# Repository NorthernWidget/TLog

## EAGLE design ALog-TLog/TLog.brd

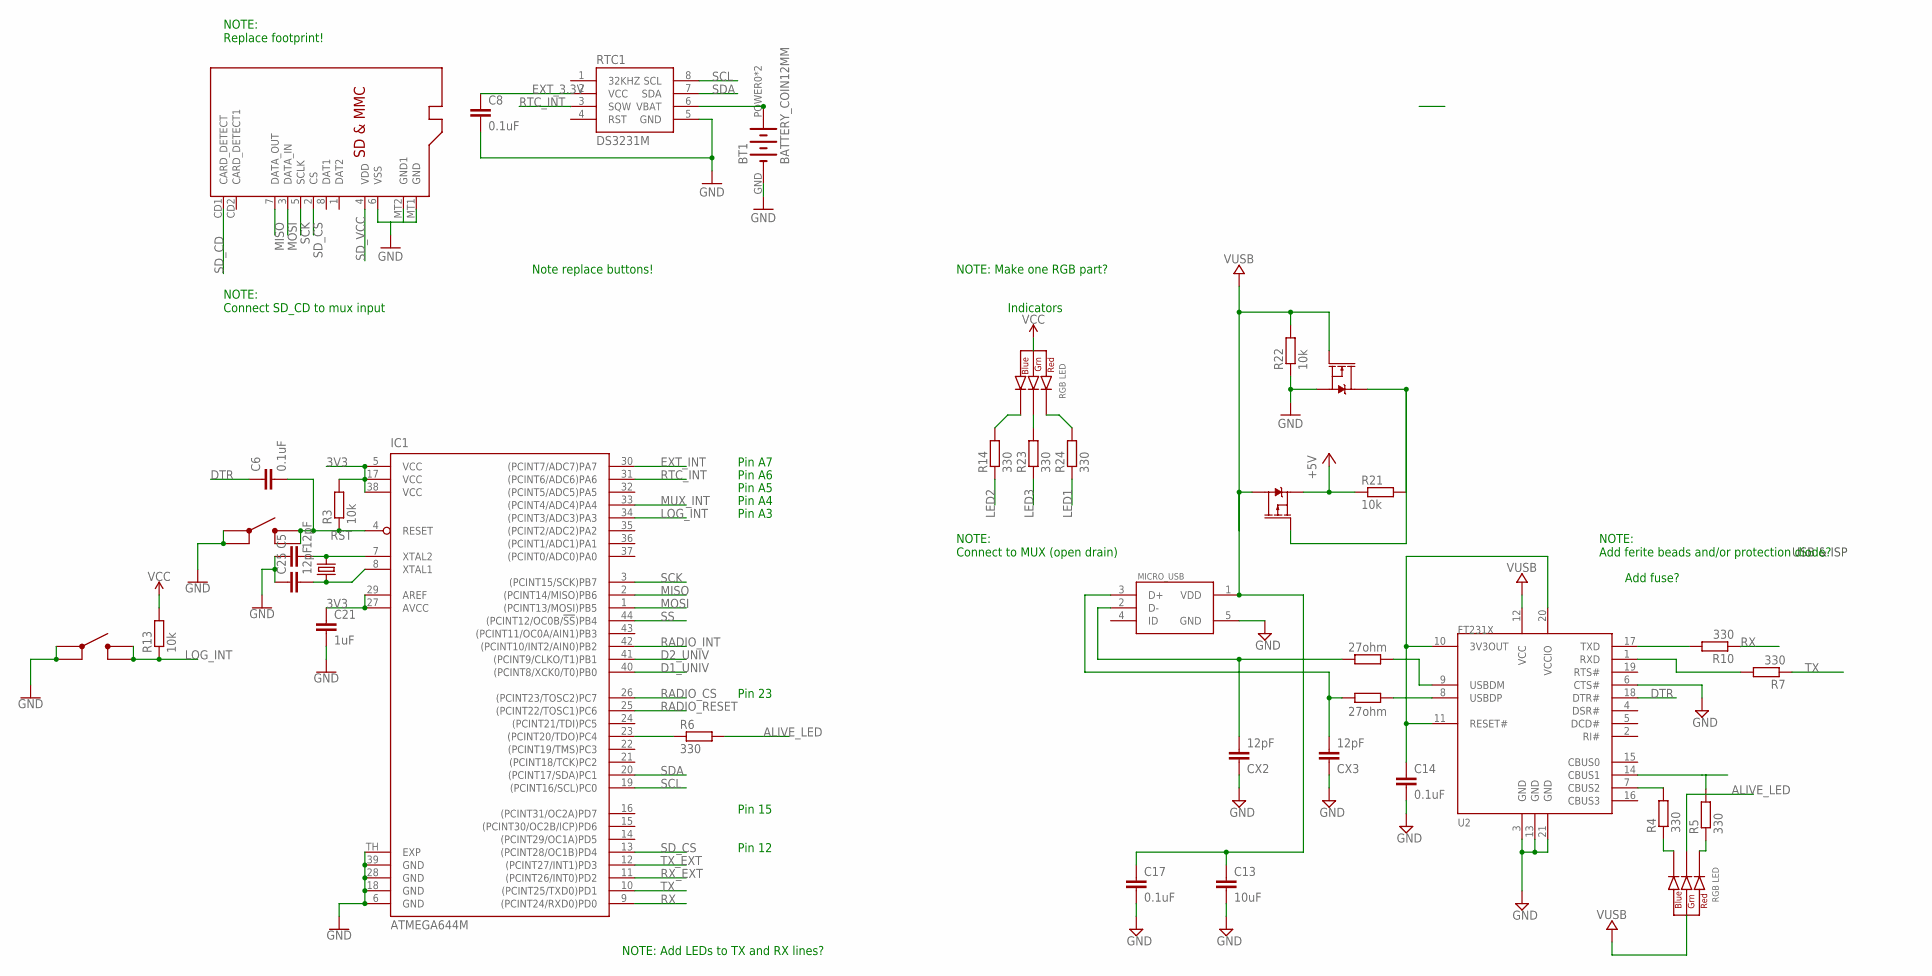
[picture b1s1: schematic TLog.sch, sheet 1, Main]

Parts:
BT1: BATTERY_COIN12MM; AWICKERT_LINX_BAT-HLD-012-SMT
C5, C25: 12pF; C0603; MPN CL10C120JB8NNNC; DIGIKEY 1276-1254-1-ND
C6, C8, C14, C17: 0.1uF; C0603
C13: 10uF; C0805
C21: 1uF; C0603; MPN CL10B105MO8NNWC; DIGIKEY 1276-6524-1-ND
CX2, CX3: 12pF; C0603
D+: 27ohm; R0603
D-: 27ohm; R0603
IC1: ATMEGA644M; MLF44-TH
MICRO_USB: MICRO_USB_LONGPADS; 10118194-0001LF_10118194-0001LF_LONGER_PADS
Q11: MOSFET-NCH-BSS138; SOT23-3
Q12: MOSFET_PCH-IRLML2244; SOT23-3
R3, R13: 10k; R0603; DIGIKEY 311-10.0KHRCT-ND
R4, R7, R10, R14, R23, R24: 330; R0603; MPN RC0603FR-07330RL
R5: 330; R0603; MPN RC0603FR-07330RL; DIGIKEY 311-330HRCT-ND
R6: 330; R0603
R21, R22: 10k; R0603
RTC1: DS3231M; SO08
U2: FT231X-Q; QFN20
U$1: CRYSTAL_5X3.2_2LEAD8MHZ; CRYSTAL_5X3.2_2-SMD
U$2: MICROSD
U$5, U$9: BUTTON4.2X3.2; SWITCH_4.2X3.2
U$15, U$16: CLVBA-FKA

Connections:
3V3: C21.1, IC1.5 (VCC), IC1.17 (VCC), IC1.27 (AVCC), IC1.29 (AREF), IC1.38 (VCC), R3.2, R13.2, U$15.2 (ANODE); also elsewhere on the board
5V: Q12.2 (S), R21.1, U$16.2 (ANODE); also elsewhere on the board
ALIVE_LED: R6.2, U$16.4 (GREEN_CATH)
D1_UNIV: IC1.40 ((PCINT8/XCK0/T0)PB0); also elsewhere on the board
D2_UNIV: IC1.41 ((PCINT9/CLKO/T1)PB1); also elsewhere on the board
DTR: C6.1, U2.18 (DTR#)
EXT_3.3V: C8.1, RTC1.2 (VCC); also elsewhere on the board
EXT_INT: IC1.30 ((PCINT7/ADC7)PA7); also elsewhere on the board
GND: BT1.GND (-), C5.1, C8.2, C13.2, C14.2, C17.2, C21.2, C25.1, CX2.1, CX3.1, IC1.6 (GND), IC1.18 (GND), IC1.28 (GND), IC1.39 (GND), IC1.TH (EXP), MICRO_USB.5 (GND), Q11.2 (S), R22.1, RTC1.5 (GND), U2.3 (GND), U2.6 (CTS#), U2.13 (GND), U2.21 (GND), U$2.6 (VSS), U$2.MT1 (GND), U$2.MT2 (GND1), U$5.1, U$5.2, U$9.1, U$9.2; also elsewhere on the board
LED1: R24.1; also elsewhere on the board
LED2: R14.1; also elsewhere on the board
LED3: R23.1; also elsewhere on the board
LOG_INT: IC1.34 ((PCINT3/ADC3)PA3), R13.1, U$5.3 (4), U$5.4 (3)
MISO: IC1.2 ((PCINT14/MISO)PB6), U$2.7 (DATA_OUT); also elsewhere on the board
MOSI: IC1.1 ((PCINT13/MOSI)PB5), U$2.3 (DATA_IN); also elsewhere on the board
MUX_INT: IC1.33 ((PCINT4/ADC4)PA4); also elsewhere on the board
unnamed: C5.2, IC1.7 (XTAL2), U$1.OSC2 (2)
unnamed: C25.2, IC1.8 (XTAL1), U$1.OSC1 (1)
unnamed: R14.2, U$15.3 (BLUE_CATH)
unnamed: R23.2, U$15.4 (GREEN_CATH)
unnamed: R24.2, U$15.1 (RED_CATH)
unnamed: R5.1, U$16.1 (RED_CATH)
unnamed: R10.2, U2.17 (TXD)
unnamed: R4.1, U$16.3 (BLUE_CATH)
unnamed: BT1.POWER0 (+), BT1.POWER1 (+), RTC1.6 (VBAT)
unnamed: IC1.23 ((PCINT20/TDO)PC4), R6.1
unnamed: Q11.3 (D), Q12.1 (G), R21.2
unnamed: R7.2, U2.1 (RXD)
unnamed: CX3.2, D+.2, MICRO_USB.3 (D+)
unnamed: CX2.2, D-.2, MICRO_USB.2 (D-)
unnamed: D+.1, U2.8 (USBDP)
unnamed: C14.1, U2.10 (3V3OUT), U2.11 (RESET#), U2.20 (VCCIO)
unnamed: R4.2, U2.7 (CBUS2)
unnamed: R5.2, U2.14 (CBUS1)
unnamed: D-.1, U2.9 (USBDM)
RADIO_CS: IC1.26 ((PCINT23/TOSC2)PC7); also elsewhere on the board
RADIO_INT: IC1.42 ((PCINT10/INT2/AIN0)PB2); also elsewhere on the board
RADIO_RESET: IC1.25 ((PCINT22/TOSC1)PC6); also elsewhere on the board
RST: C6.2, IC1.4 (RESET), R3.1, U$9.3 (4), U$9.4 (3); also elsewhere on the board
RTC_INT: IC1.31 ((PCINT6/ADC6)PA6), RTC1.3 (SQW)
RX: IC1.9 ((PCINT24/RXD0)PD0), R10.1
RX_EXT: IC1.11 ((PCINT26/INT0)PD2); also elsewhere on the board
SCK: IC1.3 ((PCINT15/SCK)PB7), U$2.5 (SCLK); also elsewhere on the board
SCL: IC1.19 ((PCINT16/SCL)PC0), RTC1.8 (SCL); also elsewhere on the board
SDA: IC1.20 ((PCINT17/SDA)PC1), RTC1.7 (SDA); also elsewhere on the board
SD_CD: U$2.CD1 (CARD_DETECT)
SD_CS: IC1.13 ((PCINT28/OC1B)PD4), U$2.2 (CS)
SD_VCC: U$2.4 (VDD); also elsewhere on the board
SS: IC1.44 ((PCINT12/OC0B/!SS!)PB4)
TX: IC1.10 ((PCINT25/TXD0)PD1), R7.1
TX_EXT: IC1.12 ((PCINT27/INT1)PD3); also elsewhere on the board
VUSB: C13.1, C17.1, MICRO_USB.1 (VDD), Q11.1 (G), Q12.3 (D), R22.2, U2.12 (VCC)

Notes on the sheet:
NOTE: Replace footprint!
Indicators
NOTE: Connect to MUX (open drain)
NOTE: Connect SD_CD to mux input
Note replace buttons!
NOTE: Make one RGB part?
Pin 12
Pin A7
Pin A6
Pin A5
Pin A4
Pin 15
NOTE: Add LEDs to TX and RX lines?
USB & ISP
Add fuse?
NOTE: Add ferite beads and/or protection diode?
Pin 23
Pin A3

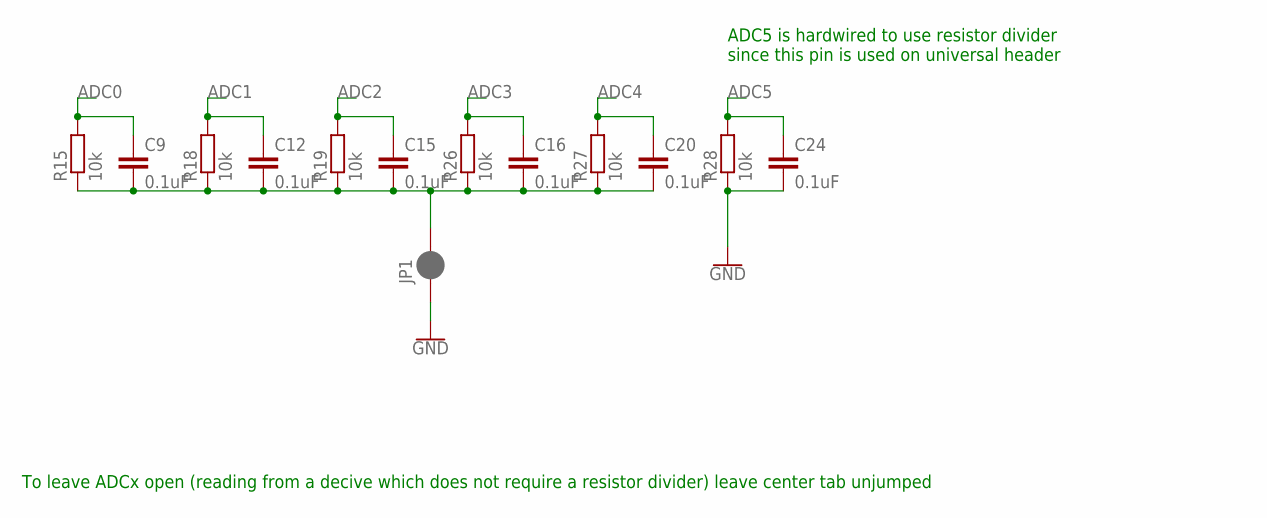
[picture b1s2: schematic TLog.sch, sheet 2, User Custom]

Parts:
C9, C12, C15, C16, C20, C24: 0.1uF; C0603
JP1: JUMPER-SMT_2_NC_PASTE_SILK; SMT-JUMPER_2_NC_PASTE_SILK
R15, R18, R19, R26, R27, R28: 10k; R0603

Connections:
ADC0: C9.1, R15.2; also elsewhere on the board
ADC1: C12.1, R18.2; also elsewhere on the board
ADC2: C15.1, R19.2; also elsewhere on the board
ADC3: C16.1, R26.2; also elsewhere on the board
ADC4: C20.1, R27.2; also elsewhere on the board
ADC5: C24.1, R28.2; also elsewhere on the board
GND: C24.2, JP1.1, R28.1; also elsewhere on the board
THERM_GND: C9.2, C12.2, C15.2, C16.2, C20.2, JP1.2, R15.1, R18.1, R19.1, R26.1, R27.1

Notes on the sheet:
To leave ADCx open (reading from a decive which does not require a resistor divider) leave center tab unjumped
ADC5 is hardwired to use resistor divider since this pin is used on universal header

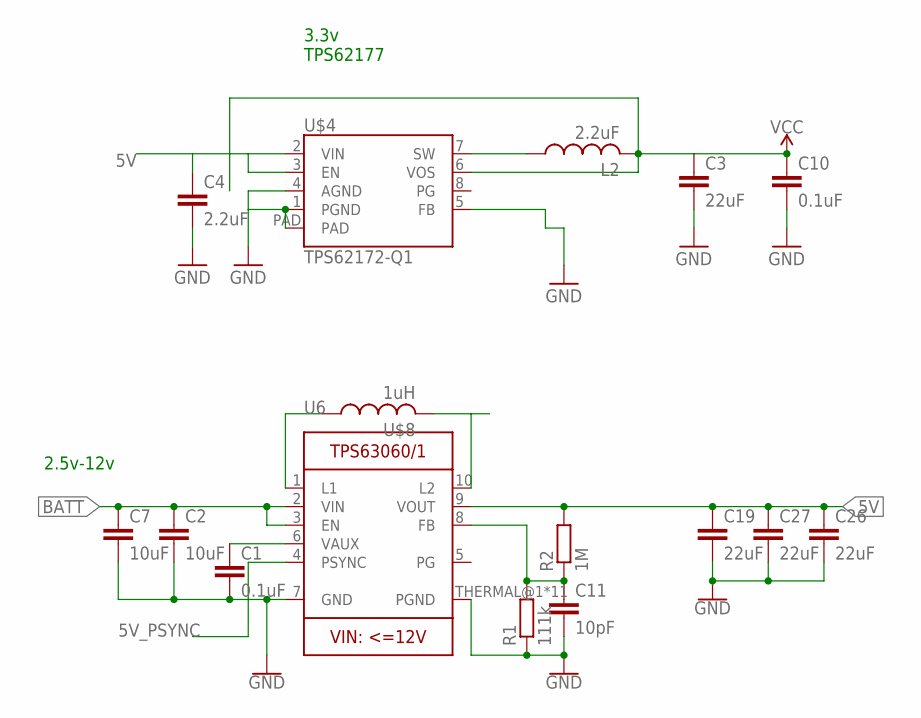
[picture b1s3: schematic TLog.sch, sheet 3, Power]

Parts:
C1, C10: 0.1uF; C0603
C2, C7: 10uF; C0805
C3, C19, C26, C27: 22uF; C0805
C4: 2.2uF; C0805
C11: 10pF; C0603
L2: 2.2uF; 0806; MPN 74438343022; DIGIKEY 732-5709-1-ND
R1: 111k; R0603; MPN RC0603FR-07143KL; DIGIKEY 311-143KHRCT-ND
R2: 1M; R0603; MPN RC0603FR-07953KL; DIGIKEY 311-953KHRCT-ND
U6: TPS63060; PWSON-N10
U$4: TPS62172-Q1; WSON-8-PAD
U$8: 1uH; WE-MAIA(4.1X4.1); MPN 78438356010; DIGIKEY 732-11310-1-ND

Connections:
3V3: C3.1, C10.1, L2.P$2 (2), U$4.6 (VOS); also elsewhere on the board
5V: C4.1, C19.1, C26.1, C27.1, R2.2, U6.9 (VOUT), U$4.2 (VIN), U$4.3 (EN); also elsewhere on the board
5V_PSYNC: U6.4 (PSYNC); also elsewhere on the board
BATT: C2.1, C7.1, U6.2 (VIN), U6.3 (EN); also elsewhere on the board
GND: C1.2, C2.2, C3.2, C4.2, C7.2, C10.2, C11.2, C19.2, C26.2, C27.2, R1.1, U6.7 (GND), U6.THERMAL@1 (PGND), U6.THERMAL@5 (PGND), U6.THERMAL@6 (PGND), U6.THERMAL@7 (PGND), U6.THERMAL@8 (PGND), U6.THERMAL@9 (PGND), U6.THERMAL@10 (PGND), U6.THERMAL@11 (PGND), U6.THERMAL@12 (PGND), U6.THERMAL@13 (PGND), U6.THERMAL@14 (PGND), U$4.1 (PGND), U$4.4 (AGND), U$4.5 (FB), U$4.PAD; also elsewhere on the board
unnamed: L2.P$1 (1), U$4.7 (SW)
unnamed: C1.1, U6.6 (VAUX)
unnamed: C11.1, R1.2, R2.1, U6.8 (FB)
unnamed: U6.1 (L1), U$8.P$1 (1)
unnamed: U6.10 (L2), U$8.P$2 (2)

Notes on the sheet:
3.3v TPS62177
2.5v-12v

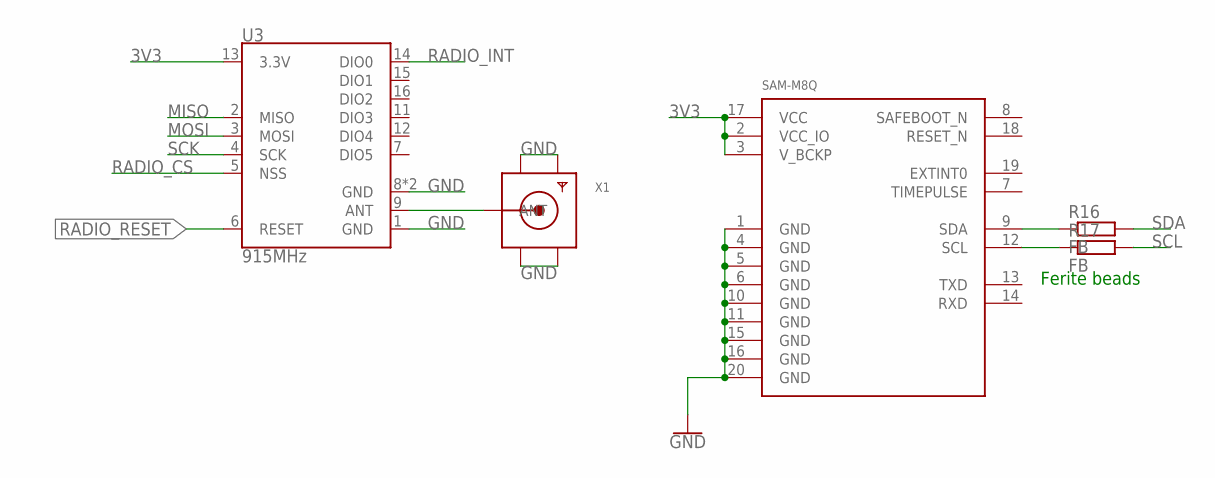
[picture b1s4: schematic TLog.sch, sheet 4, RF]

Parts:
R16, R17: FB; R0603; MPN CIC10P471NC; DIGIKEY 1276-6358-1-ND
U3: 915MHz; RFM69HCW-XXXS2
U$6: SAM-M8Q
X1: SMA_EDGE; ADAFRUIT_SMA_EDGELAUNCH

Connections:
3V3: U3.13 (3.3V), U$6.2 (VCC_IO), U$6.3 (V_BCKP), U$6.17 (VCC); also elsewhere on the board
GND: U3.1 (GND), U3.8 (GND), U3.10 (GND), U$6.1 (GND), U$6.4 (GND), U$6.5 (GND), U$6.6 (GND), U$6.10 (GND), U$6.11 (GND), U$6.15 (GND), U$6.16 (GND), U$6.20 (GND), X1.GND@1 (GND4), X1.GND@2 (GND3), X1.GND@3 (GND2), X1.GND@4 (GND1); also elsewhere on the board
MISO: U3.2 (MISO); also elsewhere on the board
MOSI: U3.3 (MOSI); also elsewhere on the board
unnamed: R16.1, U$6.9 (SDA)
unnamed: R17.1, U$6.12 (SCL)
unnamed: U3.9 (ANT), X1.P (ANT)
RADIO_CS: U3.5 (NSS); also elsewhere on the board
RADIO_INT: U3.14 (DIO0); also elsewhere on the board
RADIO_RESET: U3.6 (RESET); also elsewhere on the board
SCK: U3.4 (SCK); also elsewhere on the board
SCL: R17.2; also elsewhere on the board
SDA: R16.2; also elsewhere on the board

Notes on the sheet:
Ferite beads

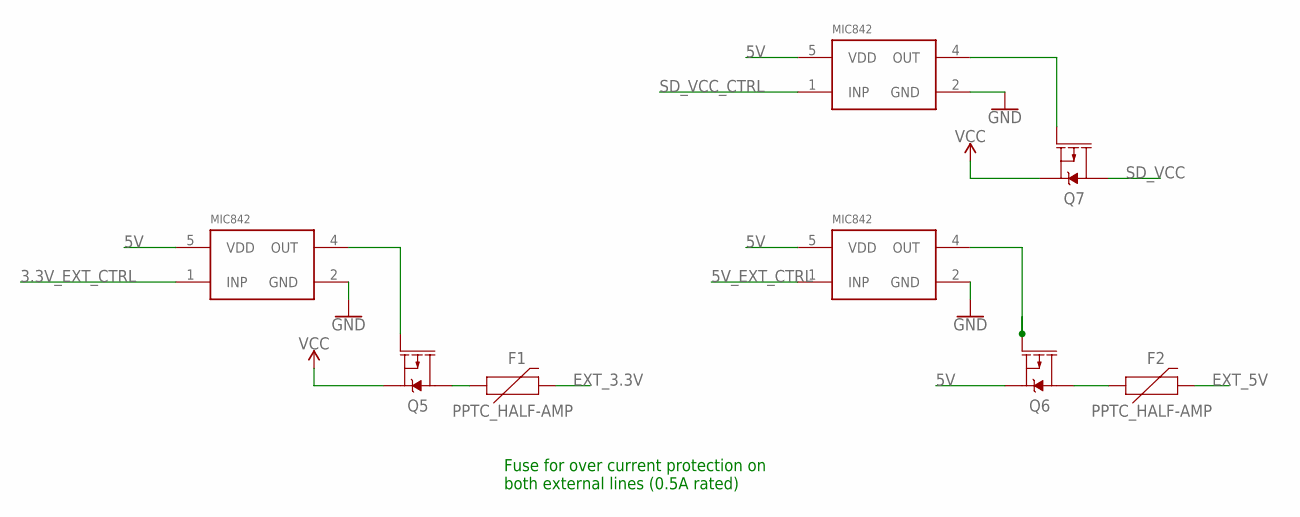
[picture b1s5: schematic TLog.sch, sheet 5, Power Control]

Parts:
F1, F2: PPTC_HALF-AMP; 1206
Q5, Q6, Q7: MOSFET_PCH-IRLML2244; SOT23-3
U$17, U$18, U$19: MIC842H; DCK_R-PDSO-G5

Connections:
3.3V_EXT_CTRL: U$18.1 (INP); also elsewhere on the board
3V3: Q5.2 (S), Q7.2 (S); also elsewhere on the board
5V: Q6.2 (S), U$17.5 (VDD), U$18.5 (VDD), U$19.5 (VDD); also elsewhere on the board
5V_EXT_CTRL: U$17.1 (INP); also elsewhere on the board
EXT_3.3V: F1.2; also elsewhere on the board
EXT_5V: F2.2; also elsewhere on the board
GND: U$17.2 (GND), U$18.2 (GND), U$19.2 (GND); also elsewhere on the board
unnamed: Q5.1 (G), U$18.4 (OUT)
unnamed: Q7.1 (G), U$19.4 (OUT)
unnamed: F1.1, Q5.3 (D)
unnamed: F2.1, Q6.3 (D)
unnamed: Q6.1 (G), U$17.4 (OUT)
SD_VCC: Q7.3 (D); also elsewhere on the board
SD_VCC_CTRL: U$19.1 (INP); also elsewhere on the board

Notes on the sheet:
Fuse for over current protection on both external lines (0.5A rated)

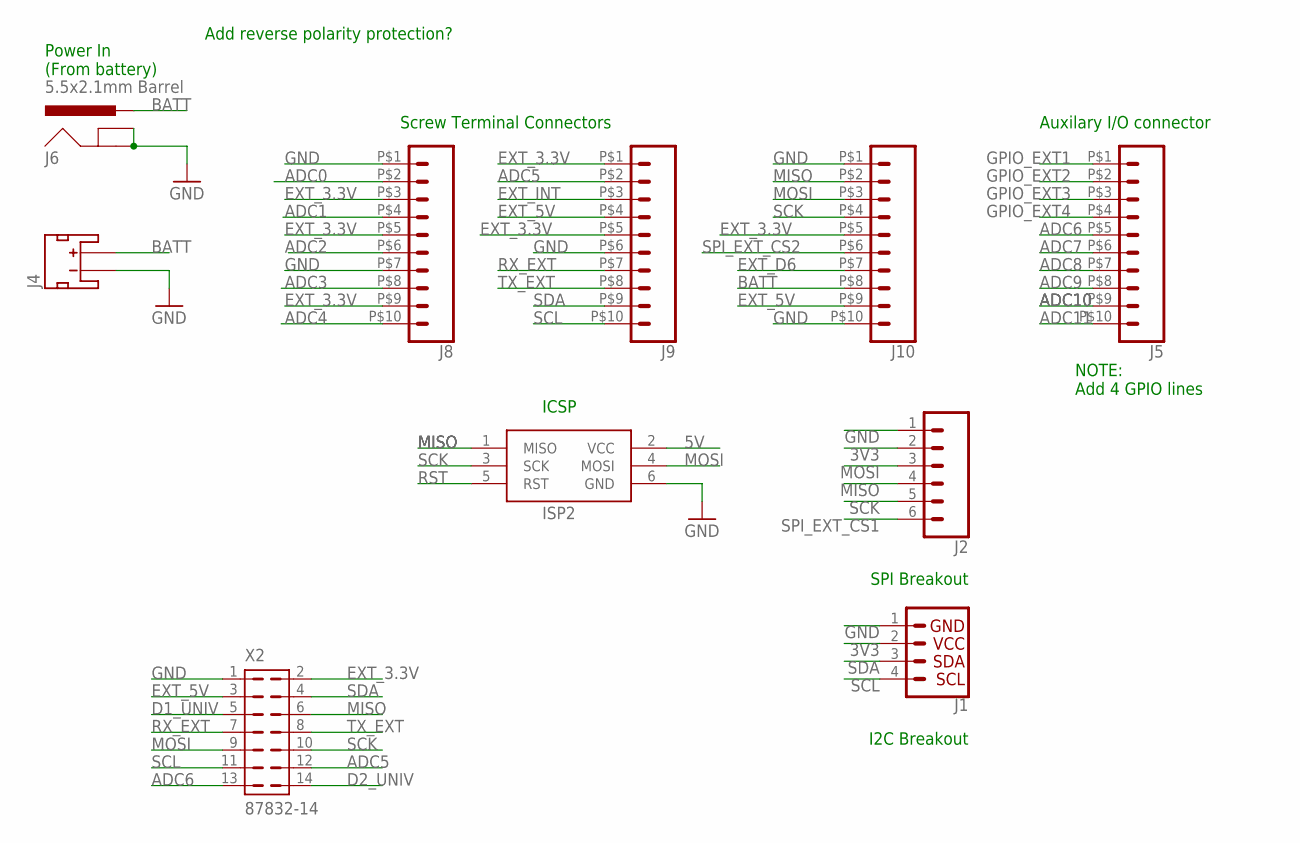
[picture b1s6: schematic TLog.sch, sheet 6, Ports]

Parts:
ISP2: AVRISP-6; AVRISP; MPN 67997-206HLF; DIGIKEY 609-3234-ND
J1: I2C_STANDARD; 1X04
J2: CONN_06SILK_FEMALE_PTH; 1X06
J4: JST_2MM_MALE; JST-2-SMD
J5, J8, J9, J10: CONN_103.5MM; 1X10_3.5MM_SCREW; MPN OSTTE100104; DIGIKEY ED2735-ND
J6: 5.5x2.1mm Barrel; POWER_JACK_SMD
X2: 87832-14; MPN 0791091006; DIGIKEY WM18702-ND

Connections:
3V3: J1.2, J2.2; also elsewhere on the board
5V: ISP2.2 (VCC); also elsewhere on the board
ADC0: J8.P$2 (2); also elsewhere on the board
ADC1: J8.P$4 (4); also elsewhere on the board
ADC2: J8.P$6 (6); also elsewhere on the board
ADC3: J8.P$8 (8); also elsewhere on the board
ADC4: J8.P$10 (10); also elsewhere on the board
ADC5: J9.P$2 (2), X2.12; also elsewhere on the board
ADC6: J5.P$5 (5), X2.13; also elsewhere on the board
ADC7: J5.P$6 (6); also elsewhere on the board
ADC8: J5.P$7 (7); also elsewhere on the board
ADC9: J5.P$8 (8); also elsewhere on the board
ADC10: J5.P$9 (9); also elsewhere on the board
ADC11: J5.P$10 (10); also elsewhere on the board
BATT: J4.2 (+), J6.VIN0 (PWR), J10.P$8 (8); also elsewhere on the board
D1_UNIV: X2.5; also elsewhere on the board
D2_UNIV: X2.14; also elsewhere on the board
EXT_3.3V: J8.P$3 (3), J8.P$5 (5), J8.P$9 (9), J9.P$1 (1), J9.P$5 (5), J10.P$5 (5), X2.2; also elsewhere on the board
EXT_5V: J9.P$4 (4), J10.P$9 (9), X2.3; also elsewhere on the board
EXT_D6: J10.P$7 (7); also elsewhere on the board
EXT_INT: J9.P$3 (3); also elsewhere on the board
GND: ISP2.6 (GND), J1.1, J2.1, J4.1 (-), J6.GND (GNDBREAK), J6.P$4 (GND), J8.P$1 (1), J8.P$7 (7), J9.P$6 (6), J10.P$1 (1), J10.P$10 (10), X2.1; also elsewhere on the board
GPIO_EXT1: J5.P$1 (1); also elsewhere on the board
GPIO_EXT2: J5.P$2 (2); also elsewhere on the board
GPIO_EXT3: J5.P$3 (3); also elsewhere on the board
GPIO_EXT4: J5.P$4 (4); also elsewhere on the board
MISO: ISP2.1 (MISO), J2.4, J10.P$2 (2), X2.6; also elsewhere on the board
MOSI: ISP2.4 (MOSI), J2.3, J10.P$3 (3), X2.9; also elsewhere on the board
RST: ISP2.5 (RST); also elsewhere on the board
RX_EXT: J9.P$7 (7), X2.7; also elsewhere on the board
SCK: ISP2.3 (SCK), J2.5, J10.P$4 (4), X2.10; also elsewhere on the board
SCL: J1.4, J9.P$10 (10), X2.11; also elsewhere on the board
SDA: J1.3, J9.P$9 (9), X2.4; also elsewhere on the board
SPI_EXT_CS1: J2.6; also elsewhere on the board
SPI_EXT_CS2: J10.P$6 (6); also elsewhere on the board
TX_EXT: J9.P$8 (8), X2.8; also elsewhere on the board

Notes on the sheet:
Power In (From battery)
Add reverse polarity protection?
I2C Breakout
SPI Breakout
Screw Terminal Connectors
ICSP
Auxilary I/O connector
NOTE: Add 4 GPIO lines

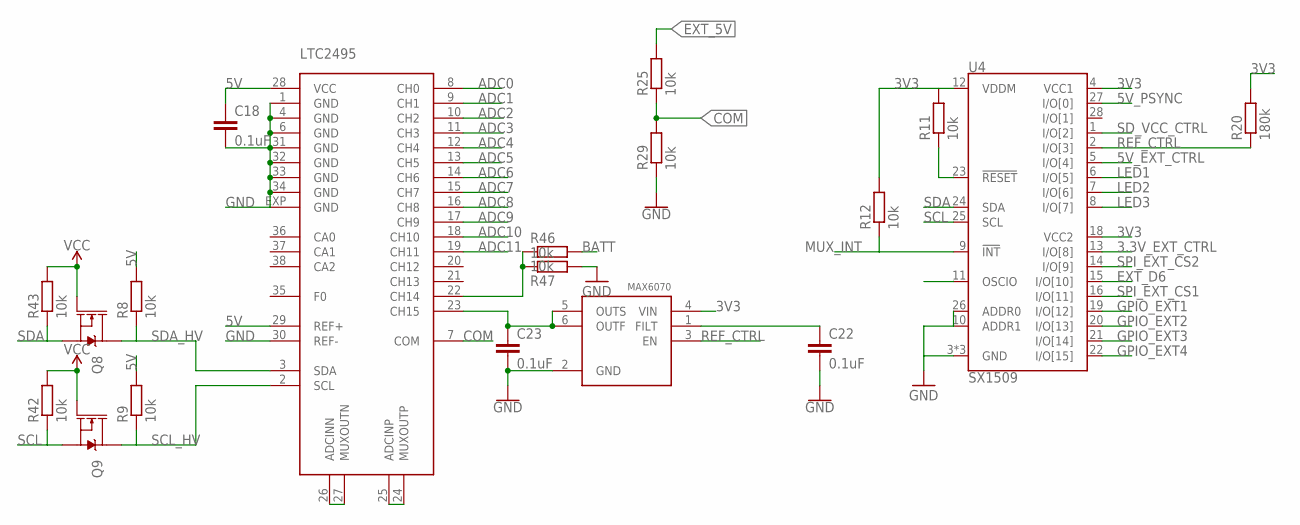
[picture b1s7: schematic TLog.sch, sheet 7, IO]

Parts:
C18, C22, C23: 0.1uF; C0603
Q8, Q9: 310mA/60V/1.6Ω; SOT323
R8, R9, R11, R12, R25, R29, R42, R43, R46, R47: 10k; R0603
R20: 180k; R0603
U4: SX1509; QFN-28
U$7: LTC2495; QFN38-5X7
U$10: MAX6070AAUT18; SOT23-6L

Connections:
3.3V_EXT_CTRL: U4.13 (I/O[8]); also elsewhere on the board
3V3: Q8.1 (G), Q9.1 (G), R11.2, R12.2, R20.2, R42.2, R43.2, U4.4 (VCC1), U4.12 (VDDM), U4.18 (VCC2), U$10.4 (VIN); also elsewhere on the board
5V: C18.1, R8.2, R9.2, U$7.28 (VCC), U$7.29 (REF+); also elsewhere on the board
5V_EXT_CTRL: U4.5 (I/O[4]); also elsewhere on the board
5V_PSYNC: U4.27 (I/O[0]); also elsewhere on the board
ADC0: U$7.8 (CH0); also elsewhere on the board
ADC1: U$7.9 (CH1); also elsewhere on the board
ADC2: U$7.10 (CH2); also elsewhere on the board
ADC3: U$7.11 (CH3); also elsewhere on the board
ADC4: U$7.12 (CH4); also elsewhere on the board
ADC5: U$7.13 (CH5); also elsewhere on the board
ADC6: U$7.14 (CH6); also elsewhere on the board
ADC7: U$7.15 (CH7); also elsewhere on the board
ADC8: U$7.16 (CH8); also elsewhere on the board
ADC9: U$7.17 (CH9); also elsewhere on the board
ADC10: U$7.18 (CH10); also elsewhere on the board
ADC11: U$7.19 (CH11); also elsewhere on the board
BATT: R46.2; also elsewhere on the board
COM: R25.1, R29.2, U$7.7 (COM)
EXT_5V: R25.2; also elsewhere on the board
EXT_D6: U4.15 (I/O[10]); also elsewhere on the board
GND: C18.2, C22.2, C23.2, R29.1, R47.2, U4.3 (GND), U4.10 (ADDR1), U4.17 (GND), U4.26 (ADDR0), U4.29 (GND), U$7.1 (GND), U$7.4 (GND), U$7.6 (GND), U$7.30 (REF-), U$7.31 (GND), U$7.32 (GND), U$7.33 (GND), U$7.34 (GND), U$7.EXP (GND), U$10.2 (GND); also elsewhere on the board
GPIO_EXT1: U4.19 (I/O[12]); also elsewhere on the board
GPIO_EXT2: U4.20 (I/O[13]); also elsewhere on the board
GPIO_EXT3: U4.21 (I/O[14]); also elsewhere on the board
GPIO_EXT4: U4.22 (I/O[15]); also elsewhere on the board
LED1: U4.6 (I/O[5]); also elsewhere on the board
LED2: U4.7 (I/O[6]); also elsewhere on the board
LED3: U4.8 (I/O[7]); also elsewhere on the board
MUX_INT: R12.1, U4.9 (!INT); also elsewhere on the board
unnamed: U$7.26 (ADCINN), U$7.27 (MUXOUTN)
unnamed: C22.1, U$10.1 (FILT)
unnamed: C23.1, U$7.23 (CH15), U$10.5 (OUTS), U$10.6 (OUTF)
unnamed: U$7.24 (MUXOUTP), U$7.25 (ADCINP)
unnamed: R46.1, R47.1, U$7.22 (CH14)
unnamed: R11.1, U4.23 (!RESET)
REF_CTRL: R20.1, U4.2 (I/O[3]), U$10.3 (EN)
SCL: Q9.2 (S), R42.1, U4.25 (SCL); also elsewhere on the board
SCL_HV: Q9.3 (D), R9.1, U$7.2 (SCL)
SDA: Q8.2 (S), R43.1, U4.24 (SDA); also elsewhere on the board
SDA_HV: Q8.3 (D), R8.1, U$7.3 (SDA)
SD_VCC_CTRL: U4.1 (I/O[2]); also elsewhere on the board
SPI_EXT_CS1: U4.16 (I/O[11]); also elsewhere on the board
SPI_EXT_CS2: U4.14 (I/O[9]); also elsewhere on the board

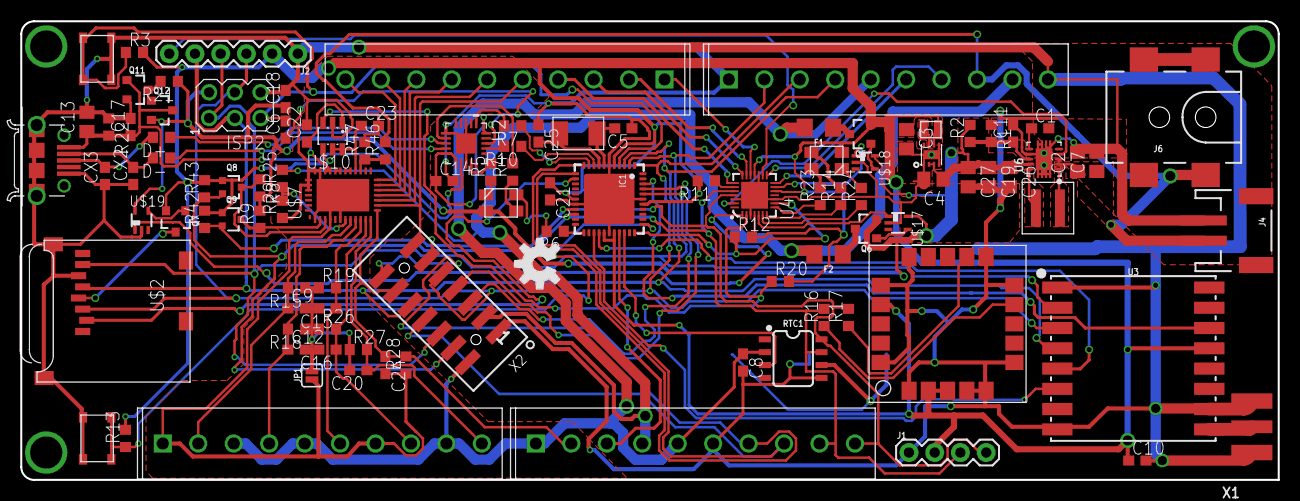
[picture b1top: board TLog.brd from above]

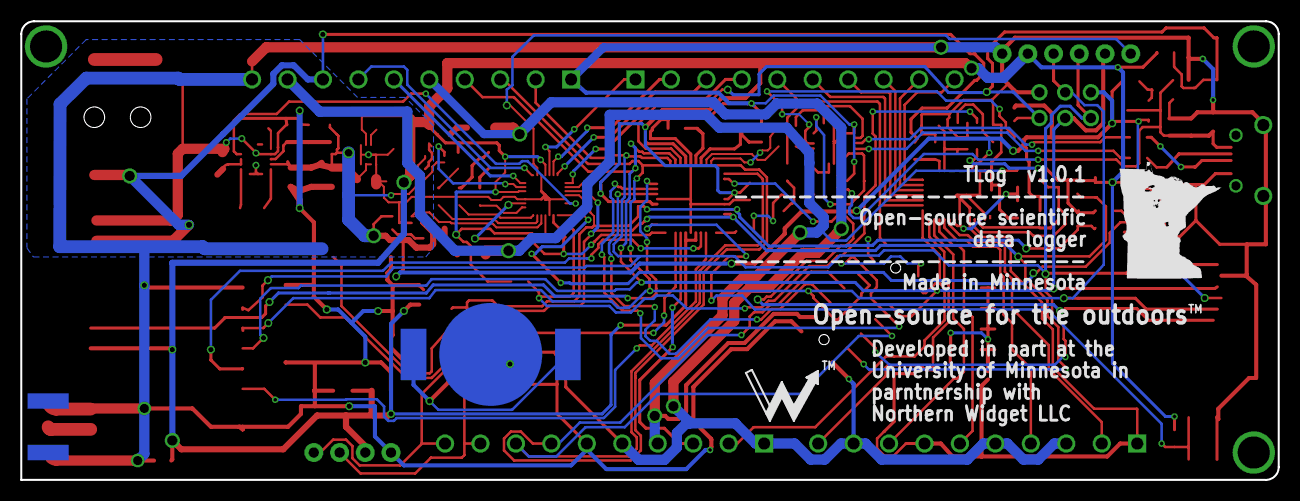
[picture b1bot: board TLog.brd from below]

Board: 2 copper layers, 124.1 x 45.3 mm, 111 parts (2 on the bottom side), 99 nets.

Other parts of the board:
LOGO1: OSHW-LOGOM; OSHW-LOGO-M
U$3: NWLOGO_MED
U$13: MN_SILK

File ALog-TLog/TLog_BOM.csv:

"Qty";"Value";"Device";"Package";"Parts";"Description";"DIGIKEY";"MF";"MPN";"OC_FARNELL";"OC_NEWARK";"PROD_ID";"SF_ID";"VALUE";
"2";"";"C-EUC0603";"C0603";"C24, C25";"CAPACITOR, European symbol";"";"";"";"";"";"";"";"";
"1";"";"CONN_06SILK_FEMALE_PTH";"1X06";"J2";"Multi connection point. Often used as Generic Header-pin footprint for 0.1 inch spaced/style header connections";"";"";"";"";"";"CONN-08437";"";"";
"4";"";"CONN_103.5MM";"1X10_3.5MM_SCREW";"J5, J8, J9, J10";"Multi connection point. Often used as Generic Header-pin footprint for 0.1 inch spaced/style header connections";"";"";"";"";"";"";"";"";
"1";"";"I2C_STANDARD";"1X04";"J1";"SparkFun I2C Standard Pinout Header";"";"";"";"";"";"";"";"";
"1";"";"JST_2MM_MALE";"JST-2-SMD";"J4";"JST 2MM MALE RA CONNECTOR";"";"";"";"";"";"CONN-11443";"PRT-08612";"";
"1";"";"R-EU_R0603";"R0603";"R6";"RESISTOR, European symbol";"";"";"";"";"";"";"";"";
"1";"";"SMACONNECTOR_EDGE";"SMA_EDGELAUNCH";"X1";"SMA Connector";"";"";"";"";"";"";"";"";
"1";".1uF";"C-EUC0603";"C0603";"C18";"CAPACITOR, European symbol";"";"";"";"";"";"";"";"";
"6";"0.1uF";"C-EUC0603";"C0603";"C1, C10, C14, C17, C22, C23";"CAPACITOR, European symbol";"";"";"";"";"";"";"";"";
"1";"10118194-0001LF_LONGER_PADS";"10118194-0001LF_LONGER_PADS";"10118194-0001LF_LONGER_PADS";"MICRO_USB";"";"";"";"";"";"";"";"";"";
"19";"10k";"R-EU_R0603";"R0603";"R3, R8, R9, R11, R12, R13, R15, R18, R19, R20, R21, R22, R26, R27, R28, R42, R43, R46, R47";"RESISTOR, European symbol";"";"";"";"";"";"";"";"";
"2";"10nF";"CCA_ECJ-1206";"CECJ-1206";"C12, C29";"CHIP CAP ARRAY";"";"";"";"";"";"";"";"";
"1";"10pF";"C-EUC0603";"C0603";"C11";"CAPACITOR, European symbol";"";"";"";"";"";"";"";"";
"1";"10uF";"C-EUC0603";"C0603";"C2";"CAPACITOR, European symbol";"";"";"";"";"";"";"";"";
"1";"10uF";"CAP_POL1206";"EIA3216";"C13";"Capacitor Polarized";"";"";"";"";"";"";"";"";
"1";"10uH";"INDUCTORLQS_4X4";"WE-LQS(4X4)";"L2";"Genaric indcutor";"";"";"";"";"";"";"";"";
"1";"143k";"R-EU_R0603";"R0603";"R1";"RESISTOR, European symbol";"";"";"";"";"";"";"";"";
"4";"1k";"R-EU_R0603";"R0603";"R4, R5, R7, R10";"RESISTOR, European symbol";"";"";"";"";"";"";"";"";
"1";"1uF";"C-EUC0603";"C0603";"C21";"CAPACITOR, European symbol";"";"";"";"";"";"";"";"";
"1";"1uH";"INDUCTORMAIA_4.1X4.1";"WE-MAIA(4.1X4.1)";"U$8";"Genaric indcutor";"";"";"";"";"";"";"";"";
"1";"2.2uF";"C-EUC0603";"C0603";"C4";"CAPACITOR, European symbol";"";"";"";"";"";"";"";"";
"3";"220mA/50V/3.5Ω";"MOSFET-NCH-BSS138";"SOT23-3";"Q1, Q8, Q9";"N-channel MOSFETs";"";"";"";"";"";"TRANS-00830";"";"220mA/50V/3.5Ω";
"3";"22uF";"C-EUC0603";"C0603";"C19, C26, C27";"CAPACITOR, European symbol";"";"";"";"";"";"";"";"";
"1";"22uF";"C-EUC1210";"C1210";"C3";"CAPACITOR, European symbol";"";"";"";"";"";"";"";"";
"2";"27ohm";"R-US_R0603";"R0603";"D+, D-";"RESISTOR, American symbol";"";"";"";"";"";"";"";"";
"3";"330";"R-EU_R0603";"R0603";"R14, R23, R24";"RESISTOR, European symbol";"";"";"";"";"";"";"";"";
"2";"33pF";"C-EUC0603";"C0603";"CX2, CX3";"CAPACITOR, European symbol";"";"";"";"";"";"";"";"";
"3";"4.3A/20V/54mΩ";"MOSFET_PCH-IRLML2244";"SOT23-3";"Q5, Q6, Q7";"P-channel MOSFETs";"";"";"";"";"";"TRANS-11153";"";"4.3A/20V/54mΩ";
"1";"5.5x2.1mm Barrel";"POWER_JACKSMD";"POWER_JACK_SMD";"J6";"Power Jack Connector";"";"";"";"";"";"CONN-08106";"PRT-12748";"5.5x2.1mm Barrel";
"2";"6V/0.5A";"PPTC_HALF-AMP";"1206";"F1, F2";"Resettable Fuse PPTC";"";"";"";"";"";"RES-08585";"";"6V/0.5A";
"1";"87832-14";"87832-14";"87832-14";"X2";"Milli-Grid Header";"";"";"";"7434698";"unknown";"";"";"";
"1";"915MHz";"RFM69HCW-915";"RFM69HCW-XXXS2";"U3";"Hope RF RFM69H ISM Transceiver Module";"";"";"";"";"";"IC-11997";"";"915MHz";
"1";"953k";"R-EU_R0603";"R0603";"R2";"RESISTOR, European symbol";"";"";"";"";"";"";"";"";
"1";"ATMEGA644M";"ATMEGA644M";"MLF44-TH";"IC1";"8-bit Microcontroller with 64K Bytes In-System Programmable Flash";"";"";"ATMEGA644P-20MU";"1748528";"26R5636";"";"";"";
"1";"AVRISP-6";"AVRISP-6";"AVRISP";"ISP2";"AVR ISP HEADER";"";"";"";"";"";"";"";"";
"2";"CLVBA-FKA";"CLVBA-FKA";"CLVBA-FKA";"U$15, U$16";"Cree RGB LED, Small Package, Common Anode, CLVBA-FKA";"";"";"";"";"";"";"";"";
"1";"CRYSTAL_5X3.2_2LEAD";"CRYSTAL_5X3.2_2LEAD";"CRYSTAL_5X3.2_2-SMD";"U$1";"TXC Crystal, 5 x 3.2mm, SMD, 2 Lead";"";"";"";"";"";"";"";"";
"1";"DS3231M";"DS3231M";"SO08";"RTC1";"DS3231M Real Time Clock";"";"";"";"";"";"IC-11985";"";"";
"2";"FB";"R-EU_R0603";"R0603";"R16, R17";"RESISTOR, European symbol";"";"";"";"";"";"";"";"";
"1";"FT231X-Q";"FT231X-Q";"QFN20";"U2";"";"";"";"";"";"";"";"";"";
"1";"LINX-BAT-HLD-012-SMT-OTL";"LINX-BAT-HLD-012-SMT-OTL";"LINX_BAT-HLD-012-SMT";"BT1";"";"";"";"";"";"";"";"";"";
"1";"LTC2495";"LTC2495";"QFN38-5X7";"U$7";"LTC2495 - Sigma Delta ADC";"";"";"";"";"";"";"";"";
"1";"MAX6070";"MAX6070";"SOT23-6L";"U$10";"MAX6070 Low Noise high precision voltage referance";"";"";"";"";"";"";"";"";
"1";"MICROSD";"MICROSD";"MICROSD";"U$2";"Micro-SD / Transflash card holder with SPI pinout";"";"";"";"";"";"";"";"";
"1";"SAM-M8Q";"SAM-M8Q";"SAM-M8Q";"U$6";"SAM-M8Q, Ublox 8 series with an integrated antenna";"";"";"";"";"";"";"";"";
"2";"SKRPABE010";"SKRPABE010";"SKRPABE010_(SWITCH)";"U$5, U$9";"SPST Switch";"";"";"";"";"";"";"";"";
"1";"SX1509";"SX1509";"QFN-28";"U4";"Semtech SX1509";"";"";"";"";"";"IC-11311";"";"SX1509";
"1";"TPS6217XTPS62177";"TPS6217XTPS62177";"WSON-10";"U$4";"TPS6217x - Step Down Converter (Buck)";"296-41856-1-ND";"TI";"TPS62177DQCR";"";"";"";"";"";
"1";"TPS63061";"TPS306X";"WSON-10";"U$3";"High input voltage buck-boost converter, 2A switch current, Vin = 2.5V to 12V";"";"";"";"";"";"";"";"";

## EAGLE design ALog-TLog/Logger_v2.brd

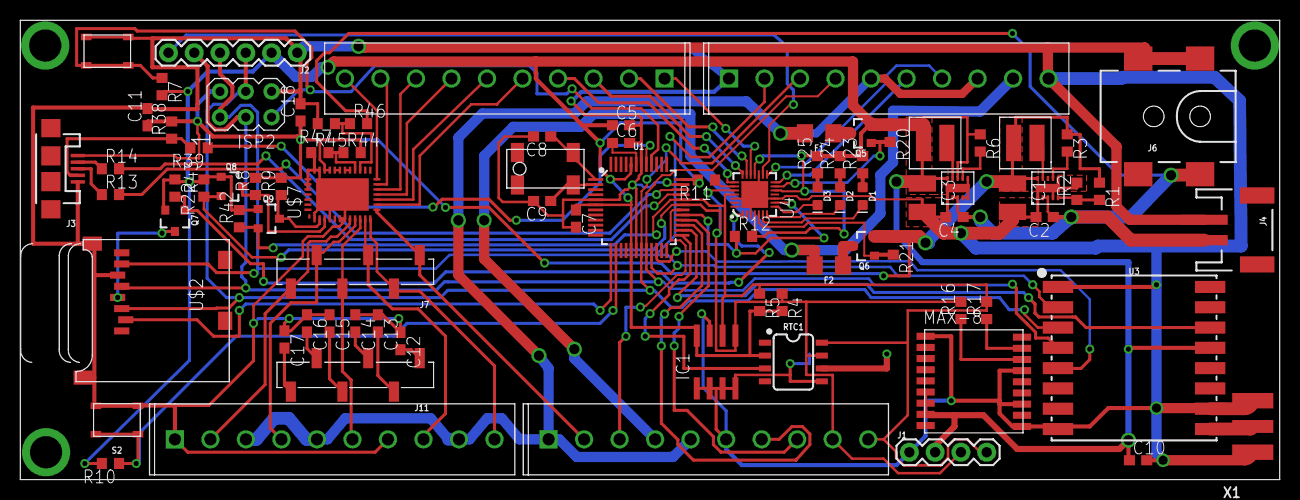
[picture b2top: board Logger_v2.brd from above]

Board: 2 copper layers, 124.1 x 45.3 mm, 87 parts (1 on the bottom side), 83 nets.

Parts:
BT1: LINX-BAT-HLD-012-SMT-OTL; LINX_BAT-HLD-012-SMT
C1, C3: 22uF; C1210
C2, C4: 2.2uF; C0603
C5, C6, C10, C11: 0.1uF; C0603
C7: 1uF; C0603
C8, C9: 12nF; C0603
C12, C13, C14, C15, C16, C17: 10nF; C0603
C18: .1uF; C0603
D1, D2, D3: LED-0603
F1, F2: 6V/0.5A; 1206
IC1: 24AA256SN; SO-08
ISP2: AVRISP-6; AVRISP
J1: 1X04
J2: 1X06
J3: USB-MICROB
J4: JST-2-SMD
J5, J8, J9, J10: SCREWTERMINAL-3.5MM-10
J6: 5.5x2.1mm Barrel; POWER_JACK_SMD
J7, J11: 1X06_SMD_STRAIGHT
L1, L2: 10uH; WE-LQS(INDUCTOR)
Q5, Q6, Q7: 4.3A/20V/54mΩ; SOT23-3
Q8, Q9: 220mA/50V/3.5Ω; SOT23-3
R1: 2M; R0603
R2: 383k; R0603
R3, R6, R38: 100k; R0603
R4, R5: 4.7k; R0603
R7, R8, R9, R10, R11, R12, R20, R21, R22, R42, R43, R44, R45, R46, R47: 10k; R0603
R13, R14, R16, R17: FB; R0603
R23, R24, R25, R39: 330; R0603
RTC1: DS3231M; SO08
S2: SKRPABE010; SKRPABE010_(SWITCH)
U1: ATSAMD21G-A; TQFP-48
U3: 915MHz; RFM69HCW-XXXS2
U4: SX1509; QFN-28
U$1: SKRPABE010; SKRPABE010_(SWITCH)
U$2: MICROSD
U$3, U$4: TPS6217X; WSON-10
U$5: CM200; 4-SOJ
U$6: UBLOX_MAX-8; MAX-8
U$7: LTC2495; QFN38-5X7
X1: SMA_EDGELAUNCH

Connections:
3.3V: C3.1, C5.1, C7.1, C10.1, IC1.8, J1.2, J2.2, L2.P$2, Q5.2, Q7.2, Q8.1, Q9.1, R4.2, R5.2, R6.1, R7.2, R10.2, R11.2, R12.2, R20.1, R22.1, R23.2, R24.2, R25.2, R42.2, R43.2, RTC1.2, U1.6, U1.17, U1.36, U1.44, U3.13, U4.4, U4.12, U4.18, U$4.P$8, U$4.P$10, U$6.P$6, U$6.P$7, U$6.P$8
3.3V_EXT_CTRL: Q5.1, R20.2, U4.13
5V: C1.1, C11.1, C18.1, ISP2.2, J3.VBUS, L1.P$2, Q6.2, R1.1, R3.1, R8.2, R9.2, R21.1, R38.2, R44.2, U$3.P$10, U$7.28, U$7.29
5V_EXT_CTRL: Q6.1, R21.2, U4.5
ADC0: J7.1, J8.P$2, U$7.8
ADC1: J7.2, J8.P$4, U$7.9
ADC2: J7.3, J8.P$6, U$7.10
ADC3: J7.4, J8.P$8, U$7.11
ADC4: J7.5, J8.P$10, U$7.12
ADC5: J7.6, J9.P$2, U$7.13
ADC6: J5.P$5, U$7.14
ADC7: J5.P$6, U$7.15
ADC8: J5.P$7, U$7.16
ADC9: J5.P$8, U$7.17
ADC10: J5.P$9, U$7.18
ADC11: J5.P$10, U$7.19
BATT+: C2.1, C4.1, J4.2, J6.VIN0, R46.2, U$3.P$2, U$3.P$3, U$4.P$2, U$4.P$3
EXT_3.3V: F1.2, J8.P$3, J8.P$5, J8.P$9, J9.P$1, J9.P$5, J10.P$5, J10.P$8
EXT_5V: F2.2, J9.P$4, J10.P$9
EXT_D6: J10.P$7, U4.15
EXT_INT: J9.P$3, U1.30
GND: BT1.GND, C1.2, C2.2, C3.2, C4.2, C5.2, C6.2, C7.2, C8.2, C9.2, C10.2, C11.2, C12.1, C13.1, C14.1, C15.1, C16.1, C17.1, C18.2, IC1.1, IC1.2, IC1.3, IC1.4, IC1.7, ISP2.6, J1.1, J2.1, J3.GND, J4.1, J6.GND, J6.P$4, J8.P$1, J8.P$7, J9.P$6, J10.P$1, J10.P$10, R2.2, R45.1, R47.2, RTC1.5, S2.P$3, S2.P$4, U1.5, U1.18, U1.35, U1.42, U3.1, U3.8, U3.10, U4.3, U4.10, U4.17, U4.26, U4.29, U$1.P$1, U$1.P$2, U$2.6, U$2.MT1, U$2.MT2, U$3.P$1, U$3.P$4, U$3.P$6, U$3.P$11, U$4.P$1, U$4.P$4, U$4.P$5, U$4.P$6, U$4.P$11, U$6.P$1, U$6.P$10, U$6.P$12, U$6.P$15, U$7.1, U$7.4, U$7.6, U$7.7, U$7.30, U$7.31, U$7.32, U$7.33, U$7.34, U$7.EXP, X1.GND@1, X1.GND@2, X1.GND@3, X1.GND@4
GPIO_EXT1: J5.P$1, U4.19
GPIO_EXT2: J5.P$2, U4.20
GPIO_EXT3: J5.P$3, U4.21
GPIO_EXT4: J5.P$4, U4.22
LED1: D1.C, U4.6
LED2: D2.C, U4.7
LED3: D3.C, U4.8
MISO: ISP2.1, J2.4, J10.P$2, U1.21, U3.2, U$2.7
MOSI: ISP2.4, J2.3, J10.P$3, U1.19, U3.3, U$2.3
MUX_INT: R12.1, U1.29, U4.9
unnamed: L1.P$1, U$3.P$9
unnamed: L2.P$1, U$4.P$9
unnamed: R1.2, R2.1, U$3.P$5
unnamed: R3.2, U$3.P$7
unnamed: R10.1, S2.P$1, S2.P$2, U1.14
unnamed: R6.2, U$4.P$7
unnamed: C6.1, U1.43
unnamed: C8.1, U1.1, U$5.P$4
unnamed: C9.1, U1.2, U$5.P$1
unnamed: U$7.26, U$7.27
unnamed: F1.1, Q5.3
unnamed: J3.D+, R13.1
unnamed: J3.D-, R14.1
unnamed: F2.1, Q6.3
unnamed: R16.1, U$6.P$16
unnamed: R17.1, U$6.P$17
unnamed: U3.9, X1.P
unnamed: BT1.POWER0, BT1.POWER1, RTC1.6
unnamed: D1.A, R23.1
unnamed: D2.A, R24.1
unnamed: D3.A, R25.1
unnamed: C12.2, J11.6
unnamed: C13.2, J11.5
unnamed: C14.2, J11.4
unnamed: C15.2, J11.3
unnamed: C16.2, J11.2
unnamed: C17.2, J11.1
unnamed: J3.ID, R38.1, R39.2
unnamed: U$7.24, U$7.25
unnamed: R44.1, R45.2, U$7.23
unnamed: R46.1, R47.1, U$7.22
unnamed: R11.1, U4.23
RADIO_CS: U1.22, U3.5
RADIO_INT: U1.26, U3.14
RST: ISP2.5, R7.1, U1.40, U$1.P$3, U$1.P$4
RTC_INT: RTC1.3, U1.25
RX_EXT: J9.P$7, U1.27
SCK: ISP2.3, J2.5, J10.P$4, U1.20, U3.4, U$2.5
SCL: IC1.6, J1.4, J9.P$10, Q9.2, R5.1, R17.2, R42.1, RTC1.8, U1.32, U4.25
SCL_HV: Q9.3, R9.1, U$7.2
SDA: IC1.5, J1.3, J9.P$9, Q8.2, R4.1, R16.2, R43.1, RTC1.7, U1.31, U4.24
SDA_HV: Q8.3, R8.1, U$7.3
SD_CS: U1.13, U$2.2
SD_VCC: Q7.3, U$2.4
SD_VCC_CTRL: Q7.1, R22.2, U4.1
SPI_EXT_CS1: J2.6, U4.16
SPI_EXT_CS2: J10.P$6, U4.14
TX_EXT: J9.P$8, U1.28
USB_D+: R13.2, U1.34
USB_D-: R14.2, U1.33
USB_HOST_EN: R39.1, U1.41

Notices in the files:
parts and their libraries:
SparkFun-LED: Licensing: Creative Commons ShareAlike 4.0 International - https://creativecommons.org/licenses/by-sa/4.0
SparkFun-Aesthetics: Licensing: CC v3.0 Share-Alike You are welcome to use this library for commercial purposes.
